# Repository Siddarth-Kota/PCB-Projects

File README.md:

This project is about designing a benchtop Lab monitor capable of monitoring noise, temperature, and humidity levels. It is connected using an ESP-32 module which manages the sensors and acts as a link
to a home internet device to monitor and graph the information.

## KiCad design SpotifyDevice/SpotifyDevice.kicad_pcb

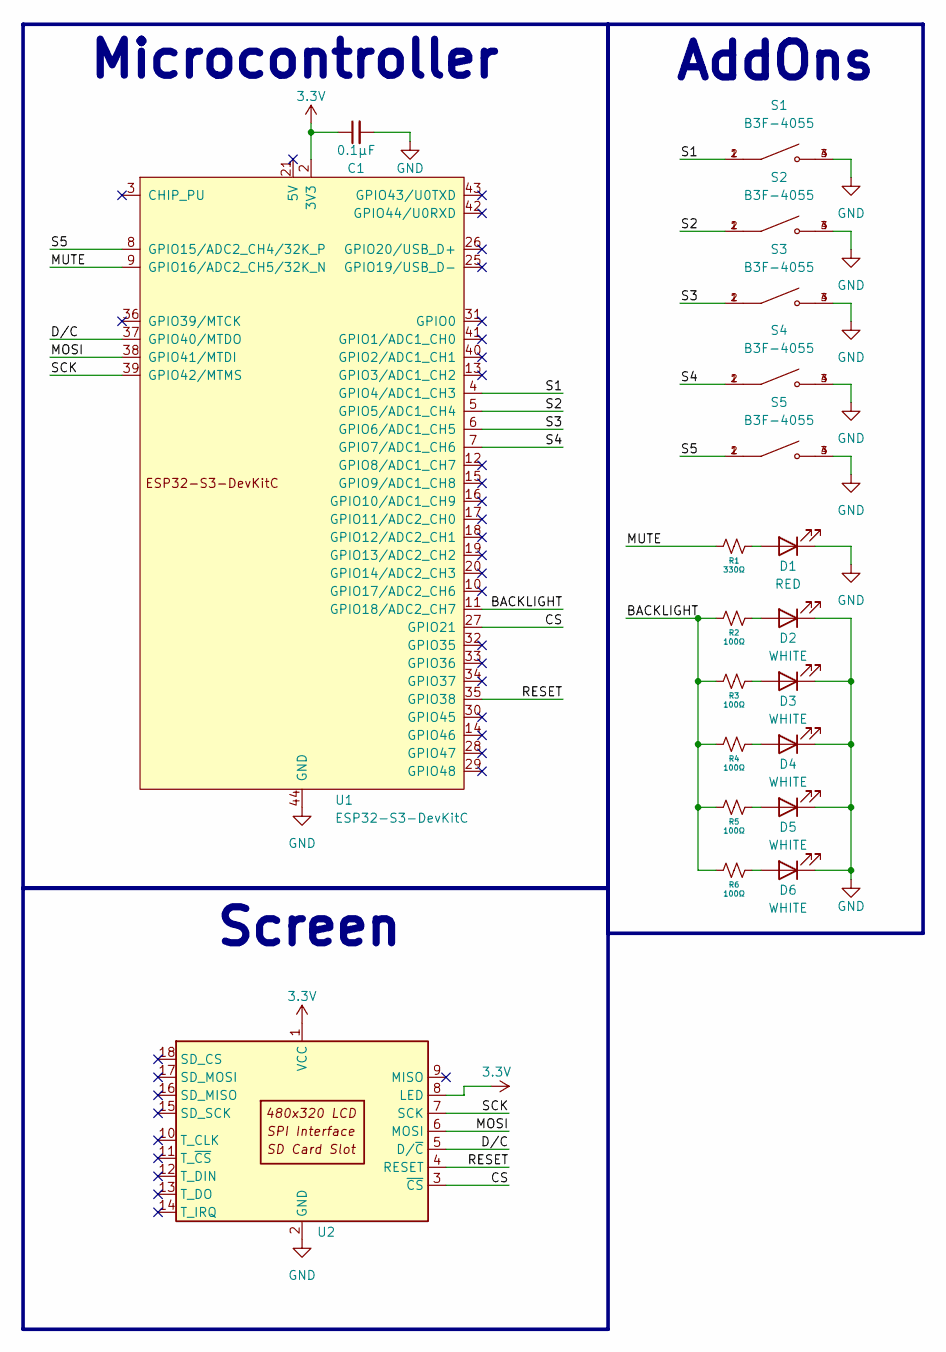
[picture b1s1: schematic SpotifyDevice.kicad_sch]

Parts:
C1: 0.1µF; C_0603_1608Metric
D1: RED; 151031SS06000
D2, D3, D4, D5, D6: WHITE; IN-S63BT5UW
R1: 330Ω; R_0603_1608Metric
R2, R3, R4, R5, R6: 100Ω; R_0603_1608Metric
S1, S2, S3, S4, S5: B3F-4055; SW_B3F-4055; PARTREV A070-E1-08
U1: ESP32-S3-DevKitC; ESP32-S3-DevKitC-1-N16R8
U2: 3.5" SPI TFT Display; 3.5_ SPI TFT Display

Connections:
3.3V: C1.1, U1.1 (3V3), U1.2 (3V3), U2.1 (VCC), U2.8 (LED)
/BACKLIGHT: R2.2, R3.2, R4.2, R5.2, R6.2, U1.11 (GPIO18/ADC2_CH7)
/CS: U1.27 (GPIO21), U2.3 (~CS)
/D/C: U1.37 (GPIO40/MTDO), U2.5 (D/~C)
/MOSI: U1.38 (GPIO41/MTDI), U2.6 (MOSI)
/MUTE: R1.2, U1.9 (GPIO16/ADC2_CH5/32K_N)
/RESET: U1.35 (GPIO38), U2.4 (RESET)
/S1: S1.1, S1.2, U1.4 (GPIO4/ADC1_CH3)
/S2: S2.1, S2.2, U1.5 (GPIO5/ADC1_CH4)
/S3: S3.1, S3.2, U1.6 (GPIO6/ADC1_CH5)
/S4: S4.1, S4.2, U1.7 (GPIO7/ADC1_CH6)
/S5: S5.1, S5.2, U1.8 (GPIO15/ADC2_CH4/32K_P)
/SCK: U1.39 (GPIO42/MTMS), U2.7 (SCK)
GND: C1.2, D1.2 (C), D2.1 (K), D3.1 (K), D4.1 (K), D5.1 (K), D6.1 (K), S1.3, S1.4, S2.3, S2.4, S3.3, S3.4, S4.3, S4.4, S5.3, S5.4, U1.22 (GND), U1.23 (GND), U1.24 (GND), U1.44 (GND), U2.2 (GND)
unnamed: D1.1 (A), R1.1
unnamed: D2.2 (A), R2.1
unnamed: D3.2 (A), R3.1
unnamed: D4.2 (A), R4.1
unnamed: D5.2 (A), R5.1
unnamed: D6.2 (A), R6.1

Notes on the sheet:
AddOns
Screen
Microcontroller

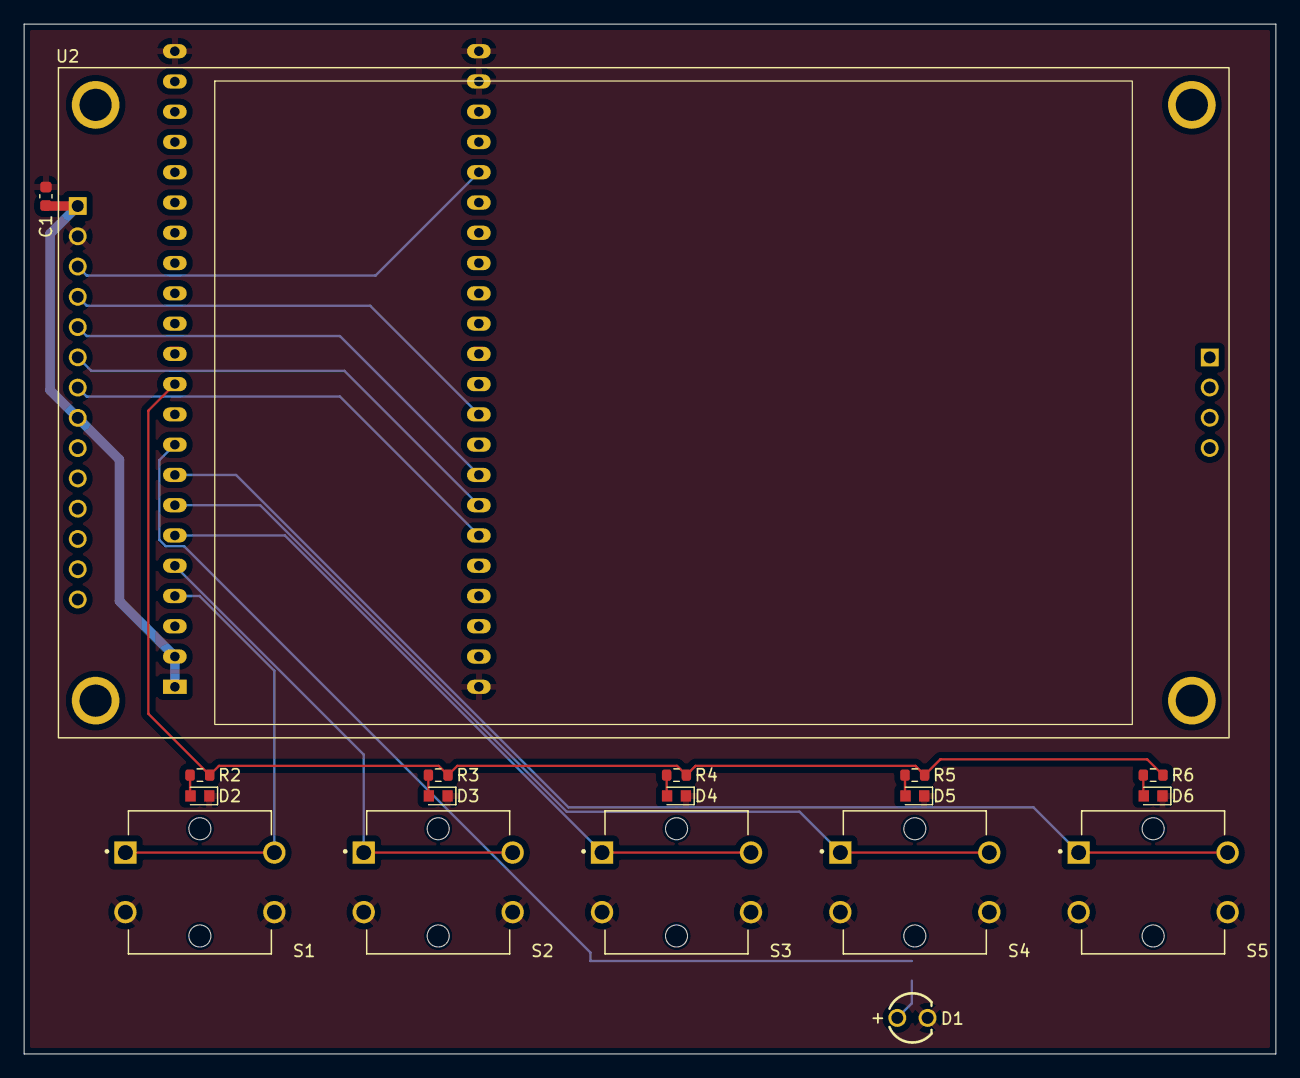
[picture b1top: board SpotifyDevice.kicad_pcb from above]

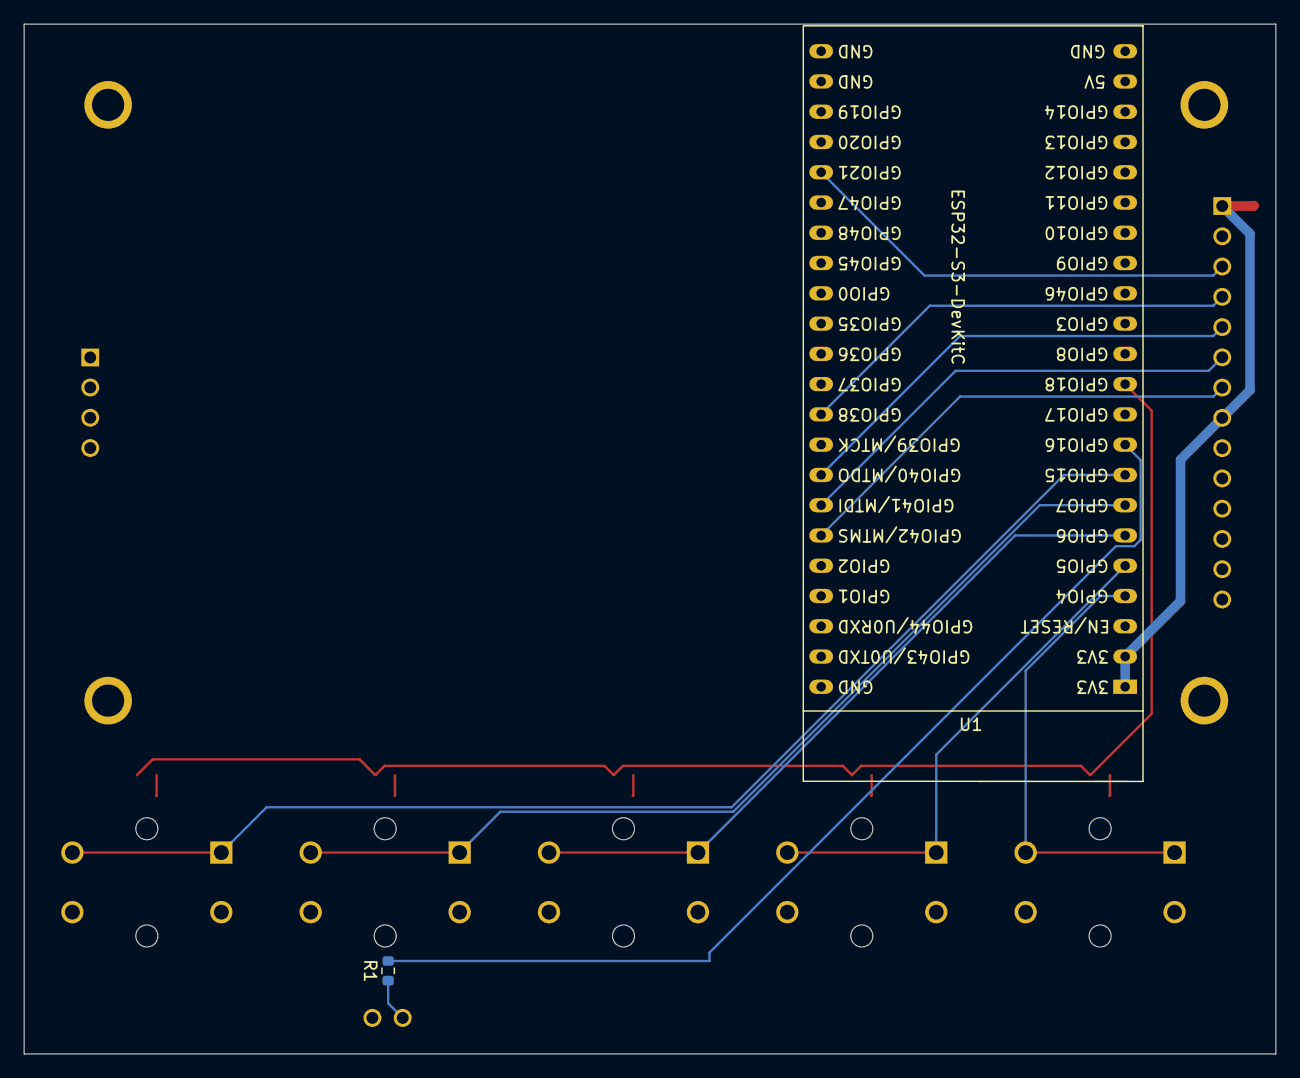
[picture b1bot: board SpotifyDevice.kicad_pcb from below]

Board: 2 copper layers, 105.1 x 86.4 mm, 20 parts (2 on the bottom side), 20 nets.

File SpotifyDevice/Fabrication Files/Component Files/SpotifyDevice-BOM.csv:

"Reference","Qty","Value","DNP","Exclude from BOM","Exclude from Board","Footprint","Datasheet"
"C1","1","0.1µF","","","","Capacitor_SMD:C_0603_1608Metric",""
"D1","1","RED","","","","ImportedParts:151031SS06000","~"
"D2,D3,D4,D5,D6","5","WHITE","","","","ImportedParts:IN-S63BT5UW","~"
"R1","1","330Ω","","","","Resistor_SMD:R_0603_1608Metric",""
"R2,R3,R4,R5,R6","5","100Ω","","","","Resistor_SMD:R_0603_1608Metric",""
"S1,S2,S3,S4,S5","5","B3F-4055","DNP","Excluded from BOM","","ImportedParts:SW_B3F-4055",""
"U1","1","ESP32-S3-DevKitC","","","","Espressif:ESP32-S3-DevKitC-1-N16R8",""
"U2","1","3.5"" SPI TFT Display","","","","ImportedParts:3.5_ SPI TFT Display",""

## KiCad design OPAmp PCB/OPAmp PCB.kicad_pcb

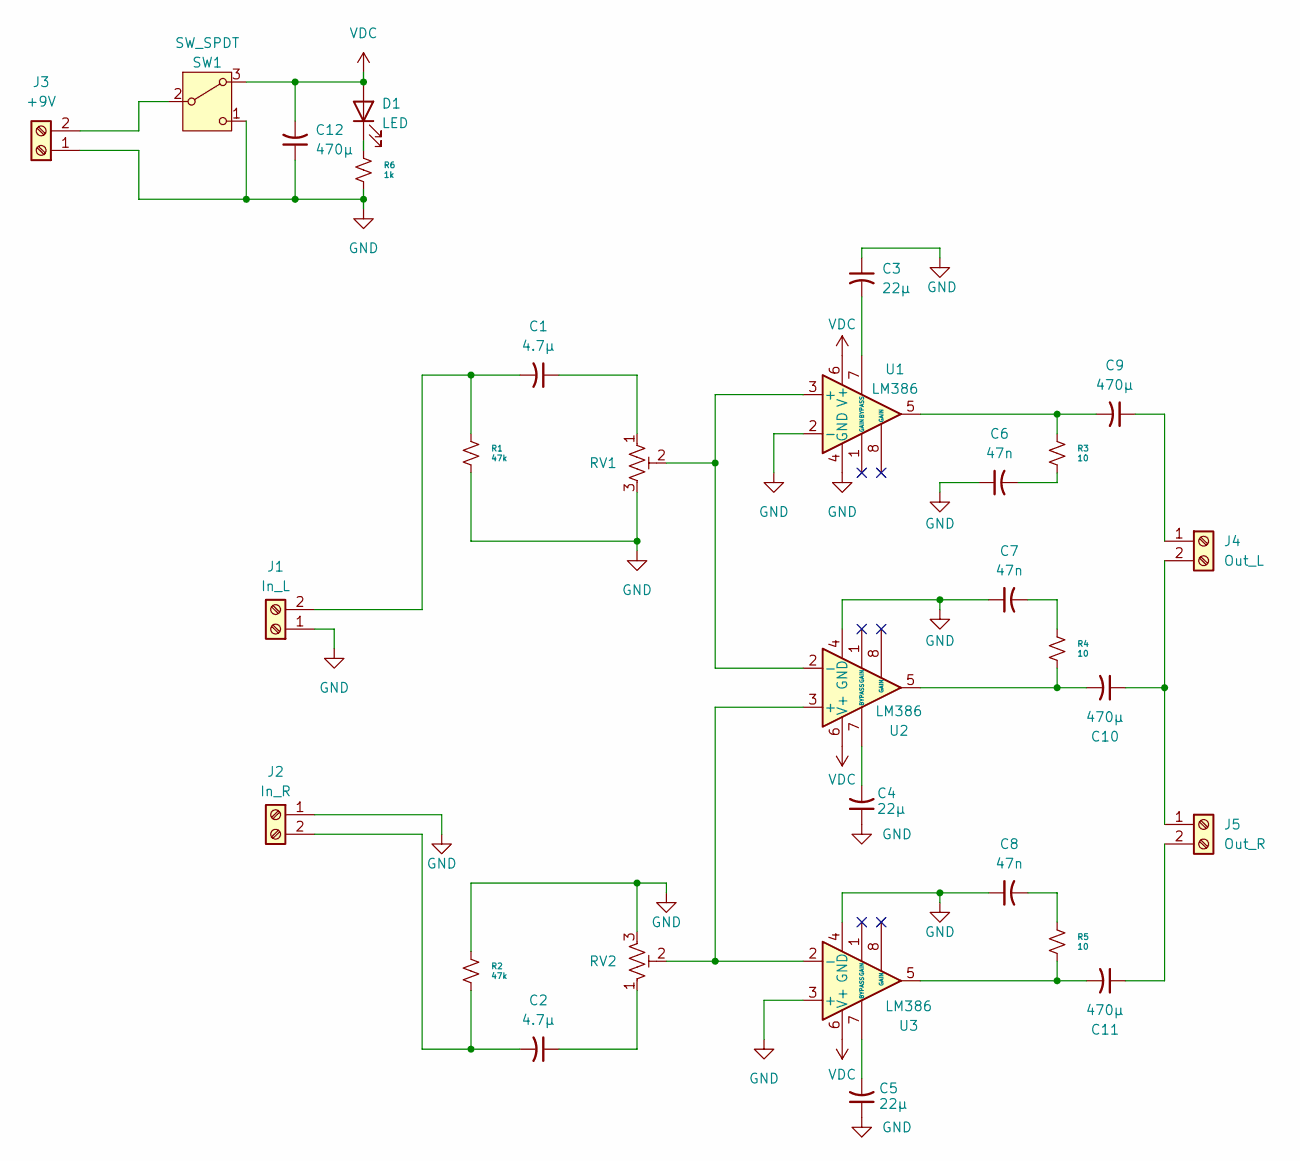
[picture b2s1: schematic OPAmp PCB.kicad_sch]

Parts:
C1, C2: 4.7μ; CP_Radial_D5.0mm_P2.50mm
C3, C4, C5: 22μ; CP_Radial_D4.0mm_P2.00mm
C6, C7, C8: 47n; C_Disc_D5.0mm_W2.5mm_P2.50mm
C9, C10, C11, C12: 470μ; CP_Radial_D10.0mm_P7.50mm
D1: LED; LED_D3.0mm
J1: In_L; TerminalBlock_MaiXu_MX126-5.0-02P_1x02_P5.00mm
J2: In_R; TerminalBlock_MaiXu_MX126-5.0-02P_1x02_P5.00mm
J3: +9V; TerminalBlock_MaiXu_MX126-5.0-02P_1x02_P5.00mm
J4: Out_L; TerminalBlock_MaiXu_MX126-5.0-02P_1x02_P5.00mm
J5: Out_R; TerminalBlock_MaiXu_MX126-5.0-02P_1x02_P5.00mm
R1, R2: 47k; R_Axial_DIN0207_L6.3mm_D2.5mm_P7.62mm_Horizontal
R3, R4, R5: 10; R_Axial_DIN0207_L6.3mm_D2.5mm_P7.62mm_Horizontal
R6: 1k; R_Axial_DIN0207_L6.3mm_D2.5mm_P7.62mm_Horizontal
RV1, RV2: R_Potentiometer_Trim_US; Potentiometer_Bourns_3386P_Vertical
SW1: SW_SPDT; SW_Slide-03_Wuerth-WS-SLTV_10x2.5x6.4_P2.54mm
U1, U2, U3: LM386; DIP-8_W7.62mm_LongPads

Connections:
GND: C3.1, C4.1, C5.1, C6.1, C7.1, C8.1, C12.1, J1.1, J2.1, J3.1, R1.2, R2.1, R6.2, RV1.3, RV2.3, SW1.1 (C), U1.2 (-), U1.4 (GND), U2.4 (GND), U3.3 (+), U3.4 (GND)
unnamed: C1.1, RV1.1
unnamed: C2.1, RV2.1
unnamed: C6.2, R3.2
unnamed: C7.2, R4.1
unnamed: C8.2, R5.1
unnamed: C9.2, R3.1, U1.5
unnamed: C10.2, R4.2, U2.5
unnamed: C11.2, R5.2, U3.5
unnamed: D1.2 (C), R6.1
unnamed: C1.2, J1.2, R1.1
unnamed: C2.2, J2.2, R2.2
unnamed: J3.2, SW1.2 (B)
unnamed: C9.1, J4.1
unnamed: C10.1, J4.2, J5.1
unnamed: C11.1, J5.2
unnamed: RV1.2, U1.3 (+), U2.2 (-)
unnamed: C3.2, U1.7 (BYPASS)
unnamed: RV2.2, U2.3 (+), U3.2 (-)
unnamed: C4.2, U2.7 (BYPASS)
unnamed: C5.2, U3.7 (BYPASS)
VDC: C12.2, D1.1 (A), SW1.3 (A), U1.6 (V+), U2.6 (V+), U3.6 (V+)

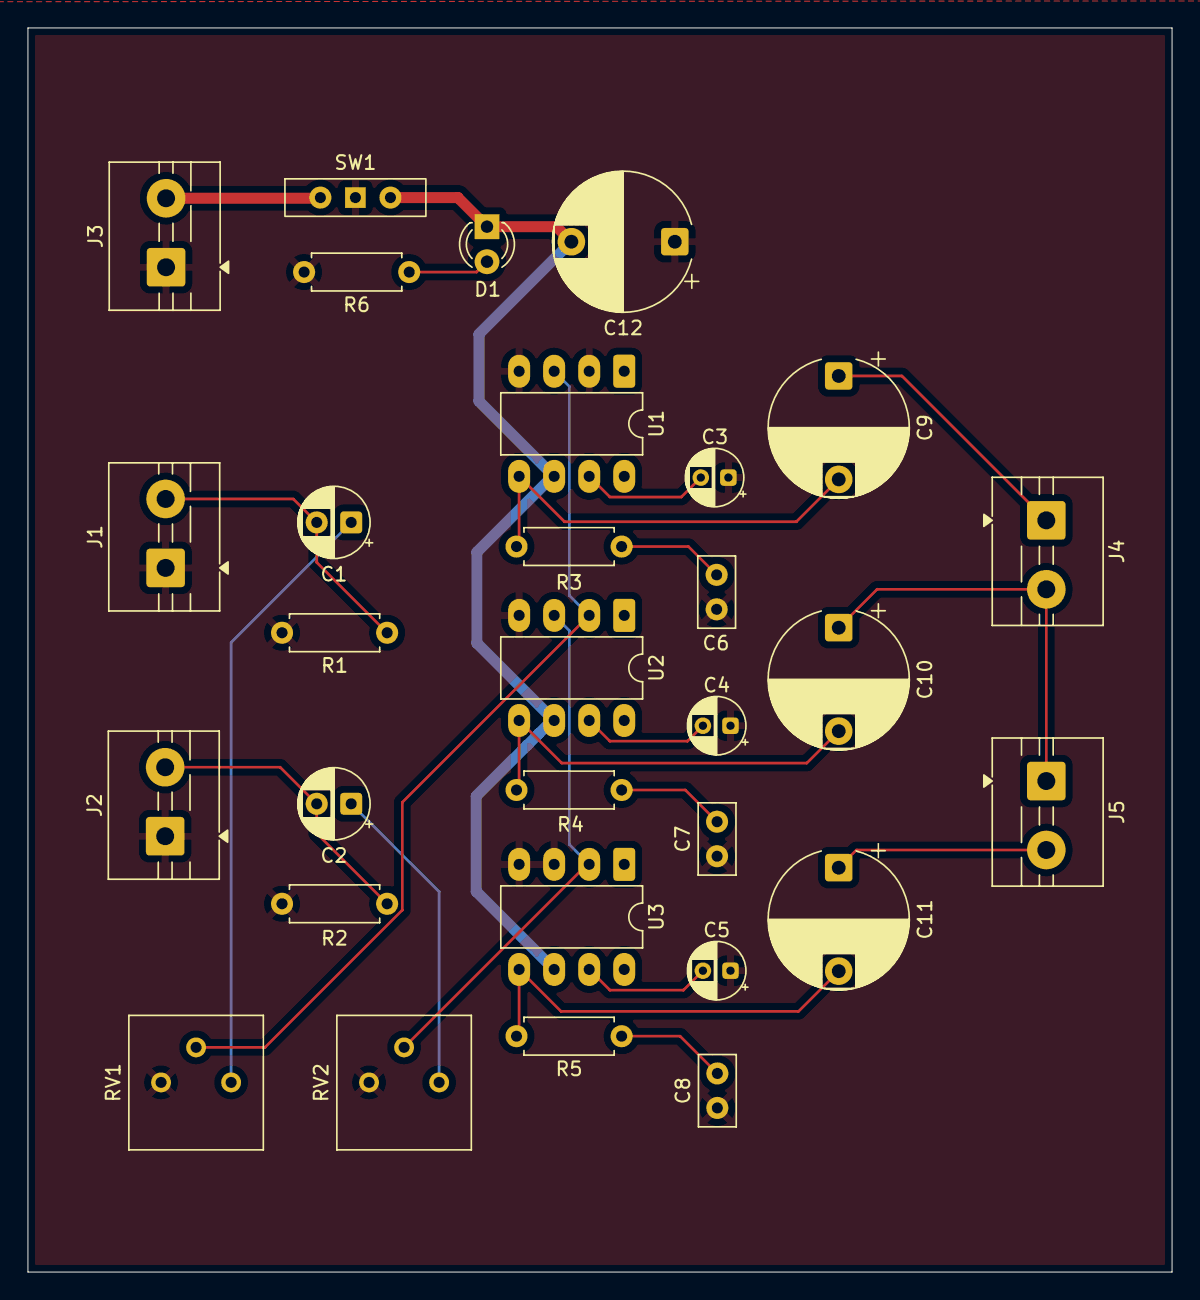
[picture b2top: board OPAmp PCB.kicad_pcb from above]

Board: 2 copper layers, 83.0 x 90.2 mm, 30 parts (0 on the bottom side), 22 nets.

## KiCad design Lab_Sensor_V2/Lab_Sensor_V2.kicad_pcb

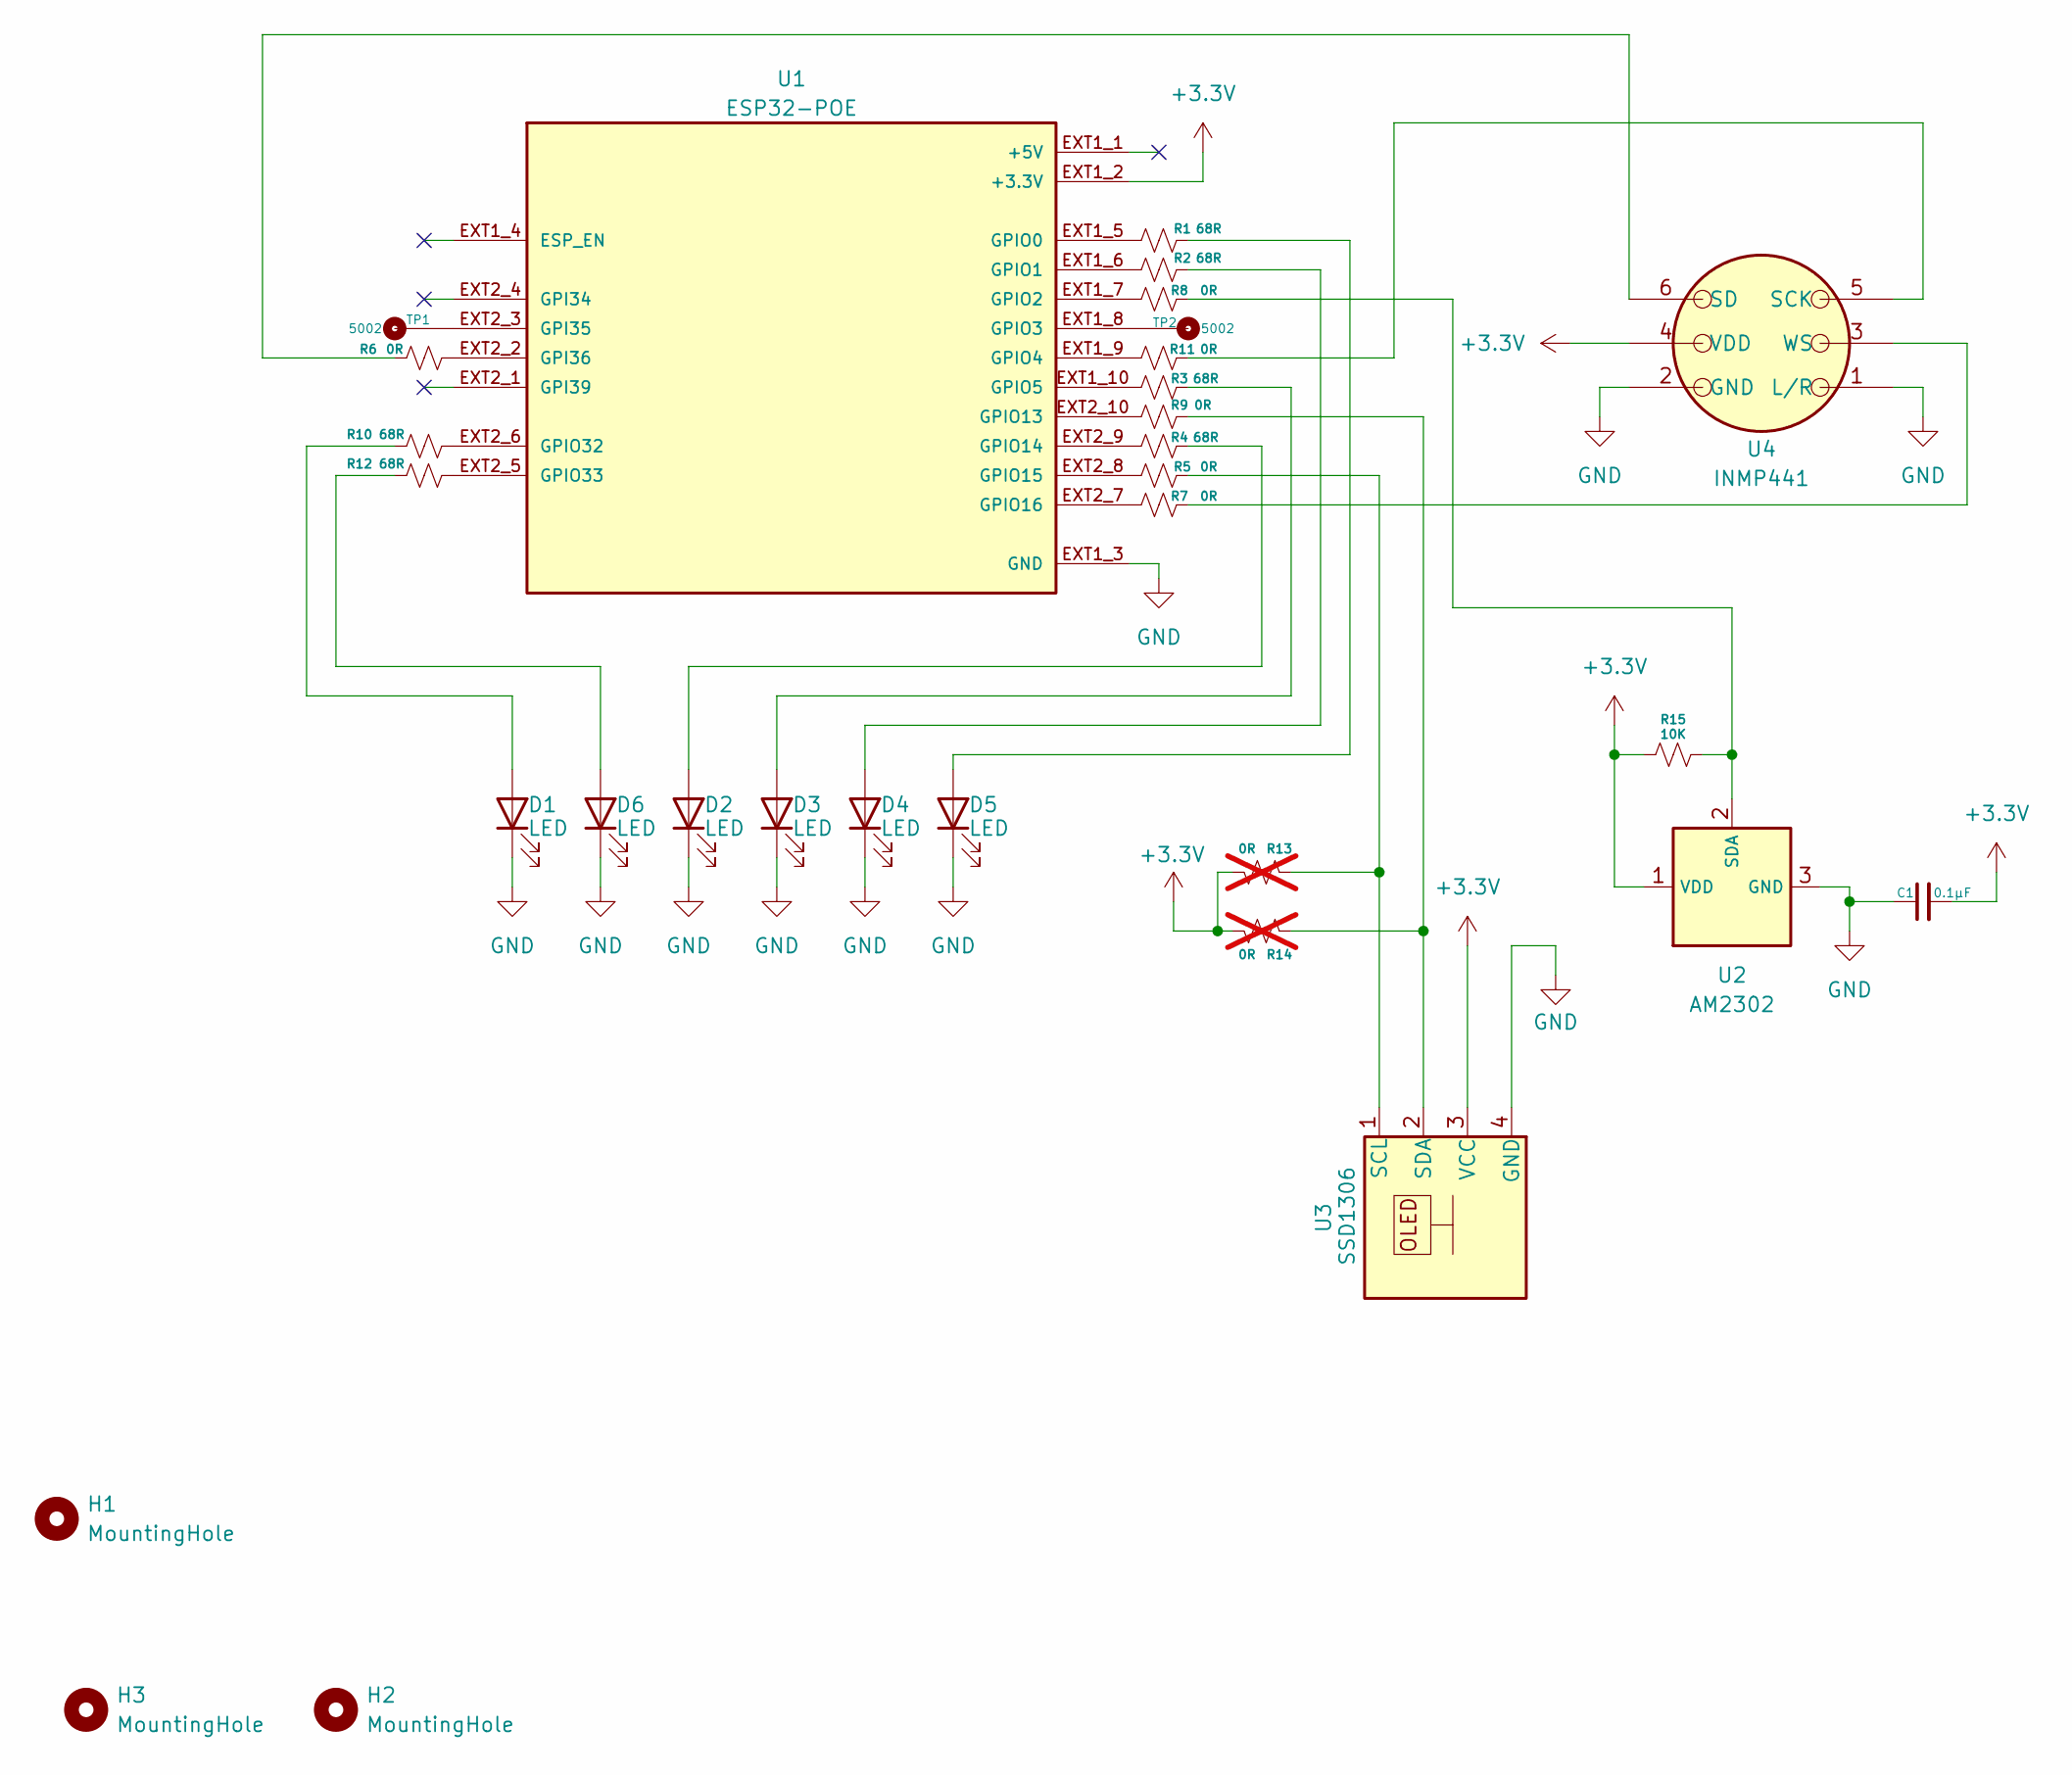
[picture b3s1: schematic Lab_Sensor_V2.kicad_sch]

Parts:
C1: 0.1µF; C_0603_1608Metric
D1, D2, D3, D4, D5, D6: LED; Standard_LED_Throughhole
H1, H2, H3: MountingHole; MountingHole_2.2mm_M2
R1, R2, R3, R4, R10, R12: 68R; R_0603_1608Metric
R5, R6, R7, R8, R9, R11: 0R; R_0603_1608Metric
R13, R14: 0R; R_0603_1608Metric; not fitted
R15: 10K; R_0603_1608Metric
TP1, TP2: 5002; PARTREV H
U1: ESP32-POE; PARTREV L1
U2: AM2302; ASAIR_AM2302_P2.54mm_Lead2.75mm_TabDown
U3: SSD1306
U4: INMP441

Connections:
+3.3V: C1.2, R13.2, R14.2, R15.2, U1.EXT1_2 (+3.3V), U2.1 (VDD), U3.3 (VCC), U4.4 (VDD)
GND: C1.1, D1.C, D2.C, D3.C, D4.C, D5.C, D6.C, U1.EXT1_3 (GND), U2.3 (GND), U2.4 (GND), U3.4 (GND), U4.1 (L/R), U4.2 (GND)
unnamed: D1.A, R10.2
unnamed: D2.A, R4.1
unnamed: D3.A, R3.1
unnamed: D4.A, R2.1
unnamed: D5.A, R1.1
unnamed: D6.A, R12.2
unnamed: TP1.TP, U1.EXT2_3 (GPI35)
unnamed: R6.1, U1.EXT2_2 (GPI36)
unnamed: R1.2, U1.EXT1_5 (GPIO0)
unnamed: R2.2, U1.EXT1_6 (GPIO1)
unnamed: R8.2, U1.EXT1_7 (GPIO2)
unnamed: TP2.TP, U1.EXT1_8 (GPIO3)
unnamed: R11.2, U1.EXT1_9 (GPIO4)
unnamed: R3.2, U1.EXT1_10 (GPIO5)
unnamed: R9.1, U1.EXT2_10 (GPIO13)
unnamed: R4.2, U1.EXT2_9 (GPIO14)
unnamed: R5.2, U1.EXT2_8 (GPIO15)
unnamed: R7.2, U1.EXT2_7 (GPIO16)
unnamed: R10.1, U1.EXT2_6 (GPIO32)
unnamed: R12.1, U1.EXT2_5 (GPIO33)
unnamed: R8.1, R15.1, U2.2 (SDA)
unnamed: R5.1, R13.1, U3.1 (SCL)
unnamed: R9.2, R14.1, U3.2 (SDA)
unnamed: R11.1, U4.5 (SCK)
unnamed: R6.2, U4.6 (SD)
unnamed: R7.1, U4.3 (WS)

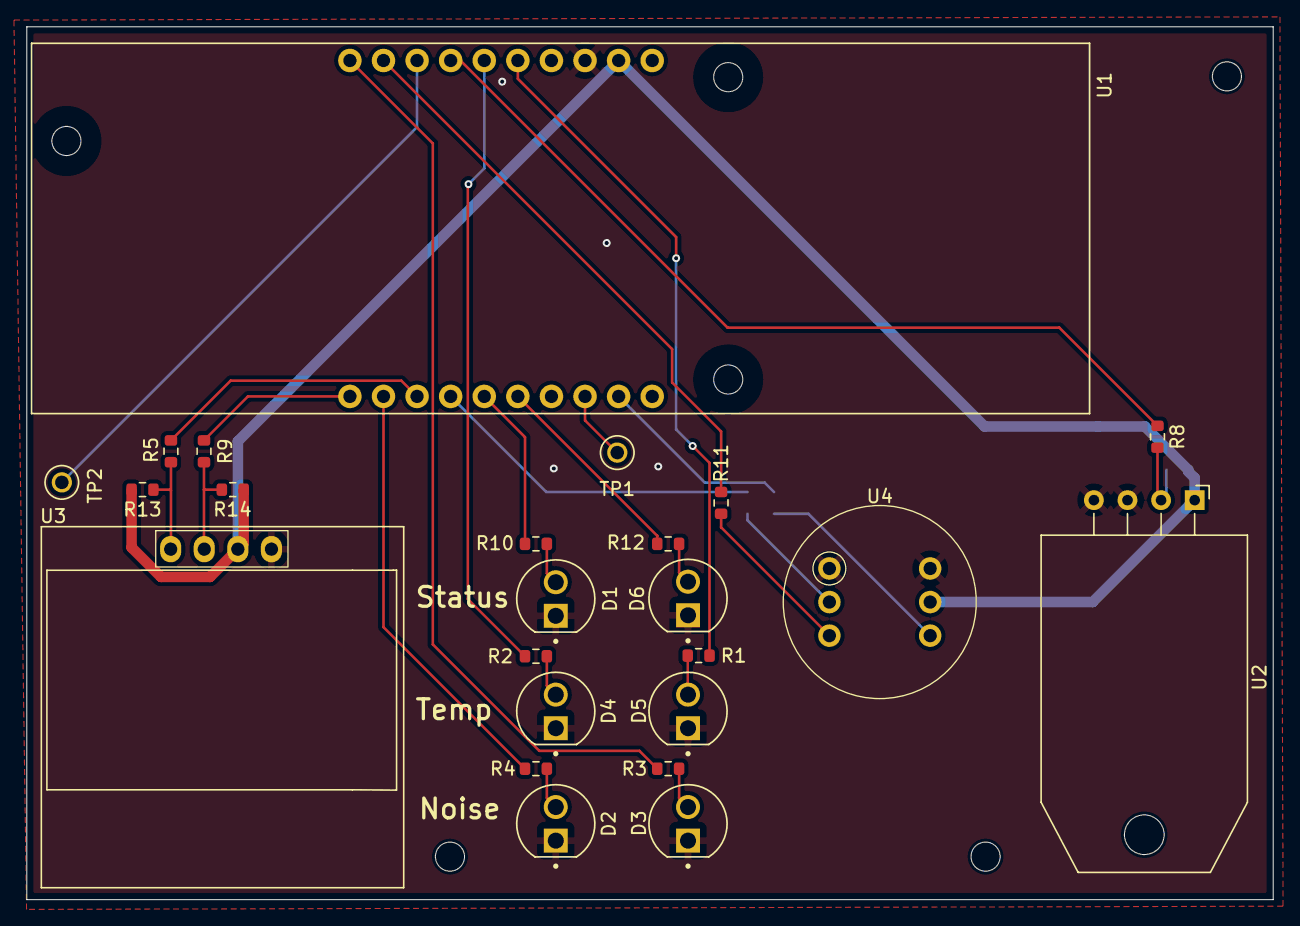
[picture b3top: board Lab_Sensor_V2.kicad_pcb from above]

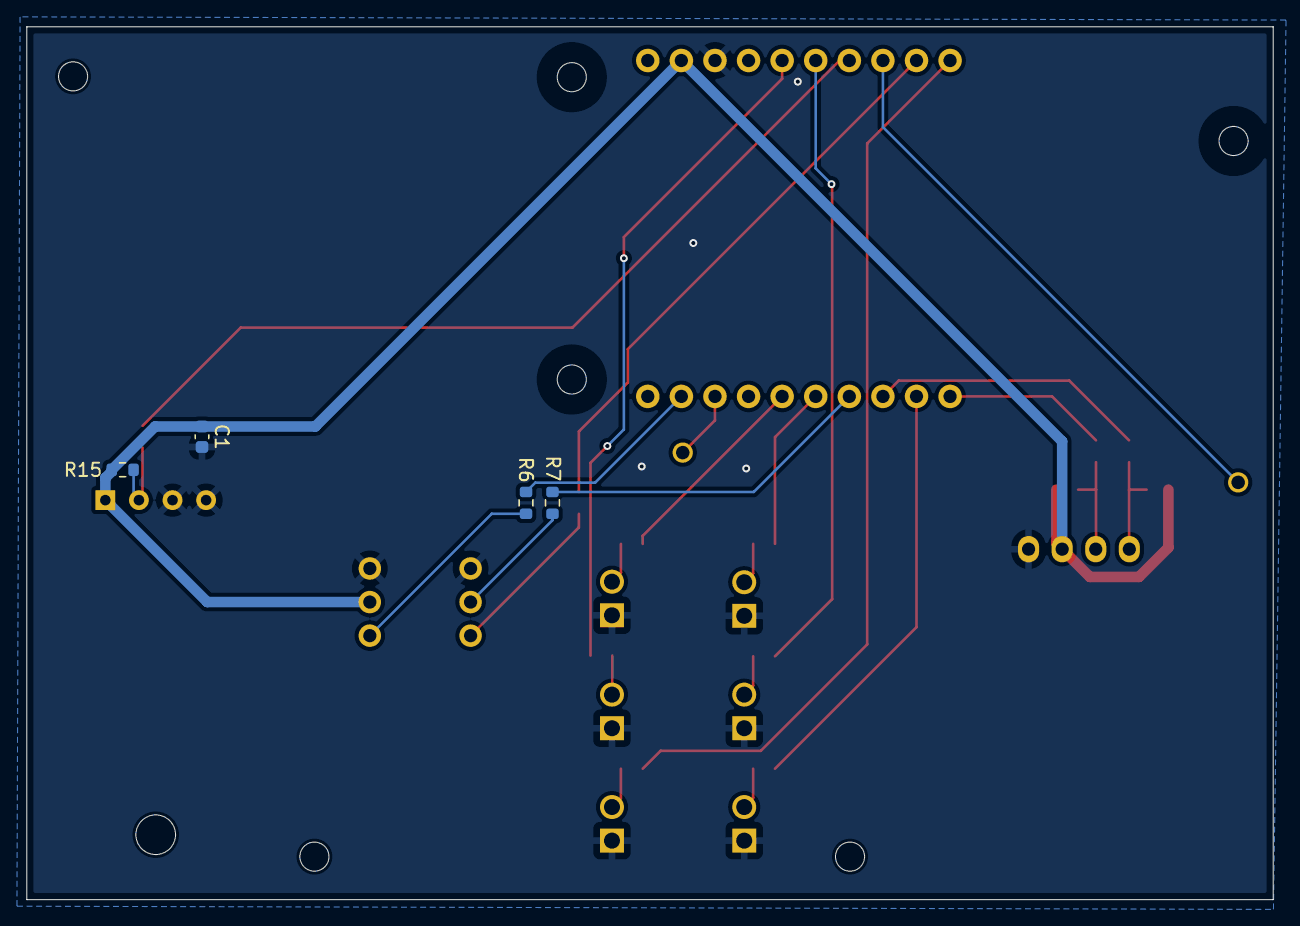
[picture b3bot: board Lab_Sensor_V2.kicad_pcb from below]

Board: 2 copper layers, 94.2 x 66.0 mm, 31 parts (4 on the bottom side), 28 nets.

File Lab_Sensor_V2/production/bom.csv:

Designator,Footprint,Quantity,Value,LCSC Part #
C1,0603,1,0.1µF,
"D1, D2, D3, D4, D5, D6",Standard_LED_Throughhole,6,LED,
"R1, R10, R12, R2, R3, R4",0603,6,68R,
"R11, R5, R6, R7, R8, R9",0603,6,0R,
R15,0603,1,10K,
"TP1, TP2",5002,2,5002,
U1,ESP32-POE,1,ESP32-POE,
U2,ASAIR_AM2302_P2.54mm_Lead2.75mm_TabDown,1,AM2302,
U3,SSD1306,1,SSD1306,
U4,INMP441,1,INMP441,

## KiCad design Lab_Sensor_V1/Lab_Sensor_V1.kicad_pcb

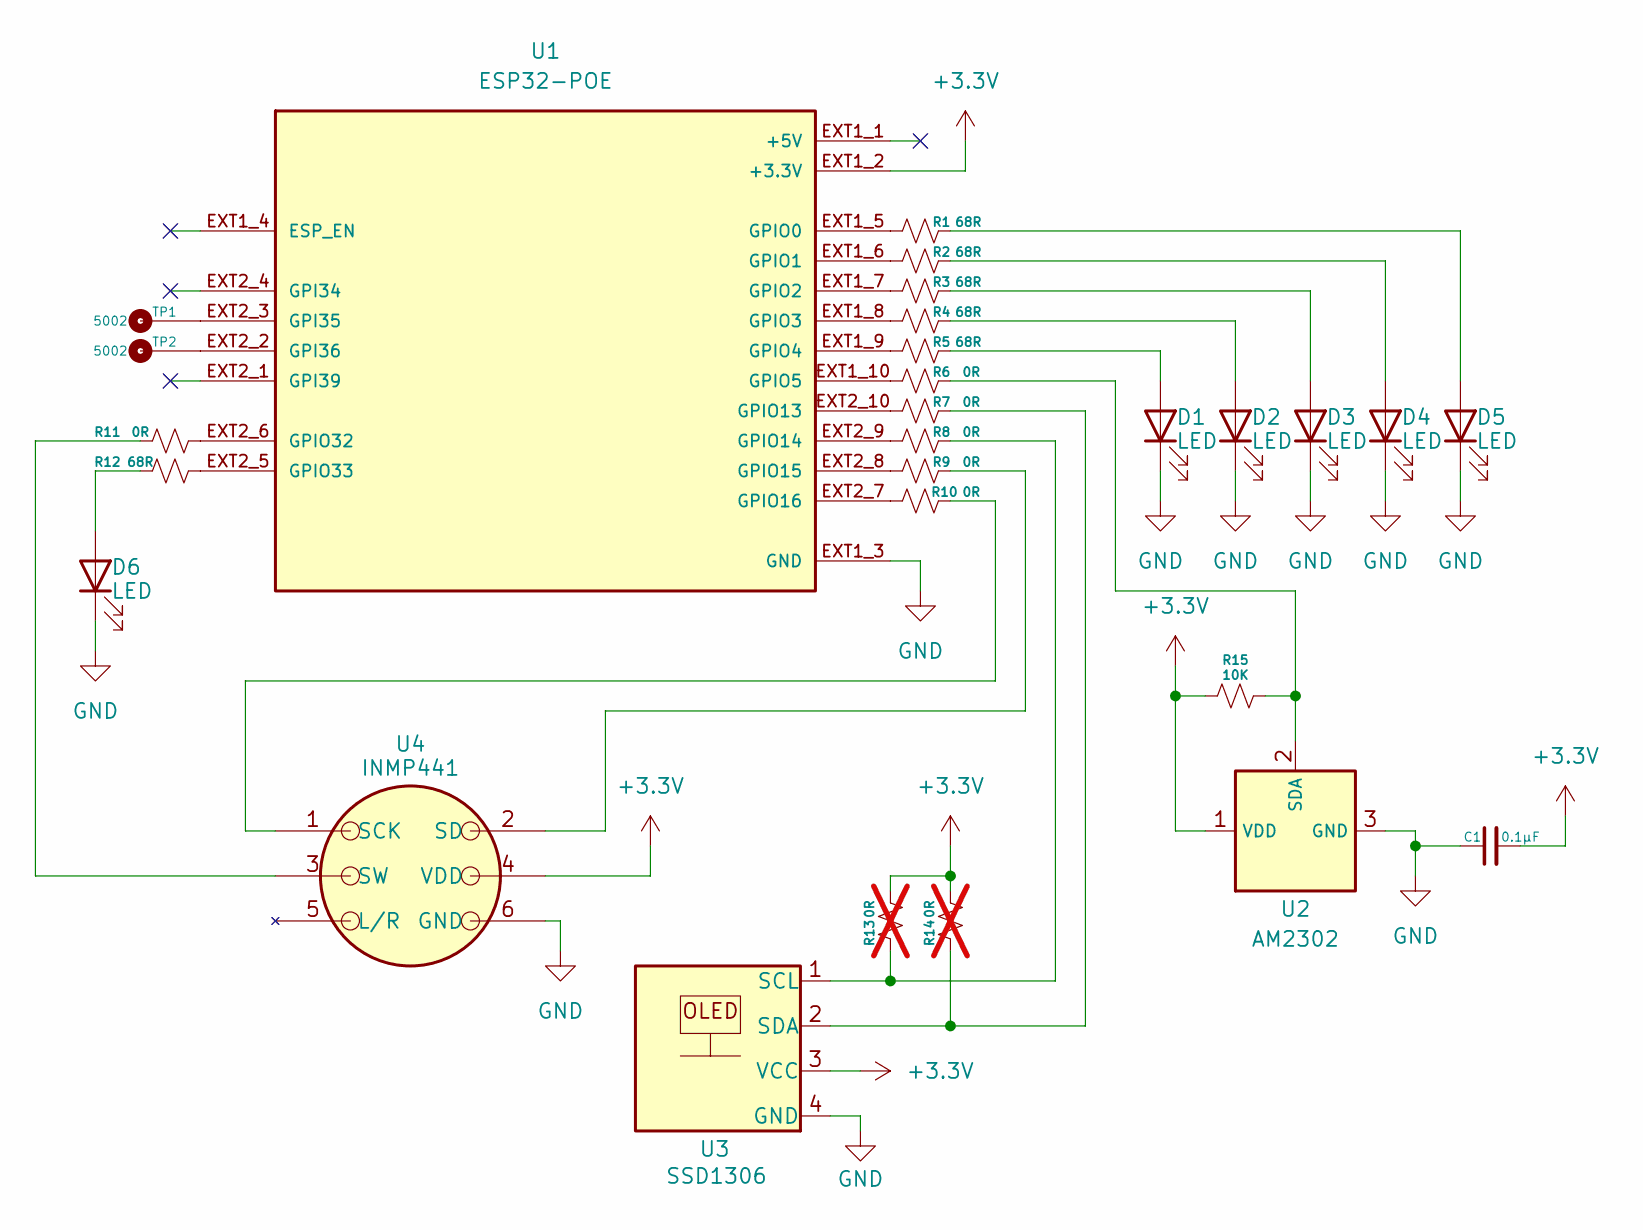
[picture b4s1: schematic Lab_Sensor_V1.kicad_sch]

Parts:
C1: 0.1µF; C_0603_1608Metric
D1, D2, D3, D4, D5, D6: LED; Standard_LED_Throughhole
R1, R2, R3, R4, R5, R12: 68R; R_0603_1608Metric
R6, R7, R8, R9, R10, R11: 0R; R_0603_1608Metric
R13, R14: 0R; R_0603_1608Metric; not fitted
R15: 10K; R_0603_1608Metric
TP1, TP2: 5002; KEYSTONE_5002; PARTREV H
U1: ESP32-POE; MODULE_ESP32-POE; PARTREV L1
U2: AM2302; ASAIR_AM2302_P2.54mm_Lead2.75mm_TabDown
U3: SSD1306; 128x64OLED
U4: INMP441

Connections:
+3.3V: C1.2, R13.1, R14.1, R15.2, U1.EXT1_2 (+3.3V), U2.1 (VDD), U3.3 (VCC), U4.4 (VDD)
GND: C1.1, D1.C, D2.C, D3.C, D4.C, D5.C, D6.C, U1.EXT1_3 (GND), U2.3 (GND), U2.4 (GND), U3.4 (GND), U4.6 (GND)
unnamed: D1.A, R5.1
unnamed: D2.A, R4.1
unnamed: D3.A, R3.1
unnamed: D4.A, R2.1
unnamed: D5.A, R1.1
unnamed: D6.A, R12.2
unnamed: TP1.TP, U1.EXT2_3 (GPI35)
unnamed: TP2.TP, U1.EXT2_2 (GPI36)
unnamed: R1.2, U1.EXT1_5 (GPIO0)
unnamed: R2.2, U1.EXT1_6 (GPIO1)
unnamed: R3.2, U1.EXT1_7 (GPIO2)
unnamed: R4.2, U1.EXT1_8 (GPIO3)
unnamed: R5.2, U1.EXT1_9 (GPIO4)
unnamed: R6.2, U1.EXT1_10 (GPIO5)
unnamed: R7.2, U1.EXT2_10 (GPIO13)
unnamed: R8.2, U1.EXT2_9 (GPIO14)
unnamed: R9.2, U1.EXT2_8 (GPIO15)
unnamed: R10.2, U1.EXT2_7 (GPIO16)
unnamed: R11.1, U1.EXT2_6 (GPIO32)
unnamed: R12.1, U1.EXT2_5 (GPIO33)
unnamed: R6.1, R15.1, U2.2 (SDA)
unnamed: R8.1, R13.2, U3.1 (SCL)
unnamed: R7.1, R14.2, U3.2 (SDA)
unnamed: R10.1, U4.1 (SCK)
unnamed: R9.1, U4.2 (SD)
unnamed: R11.2, U4.3 (SW)

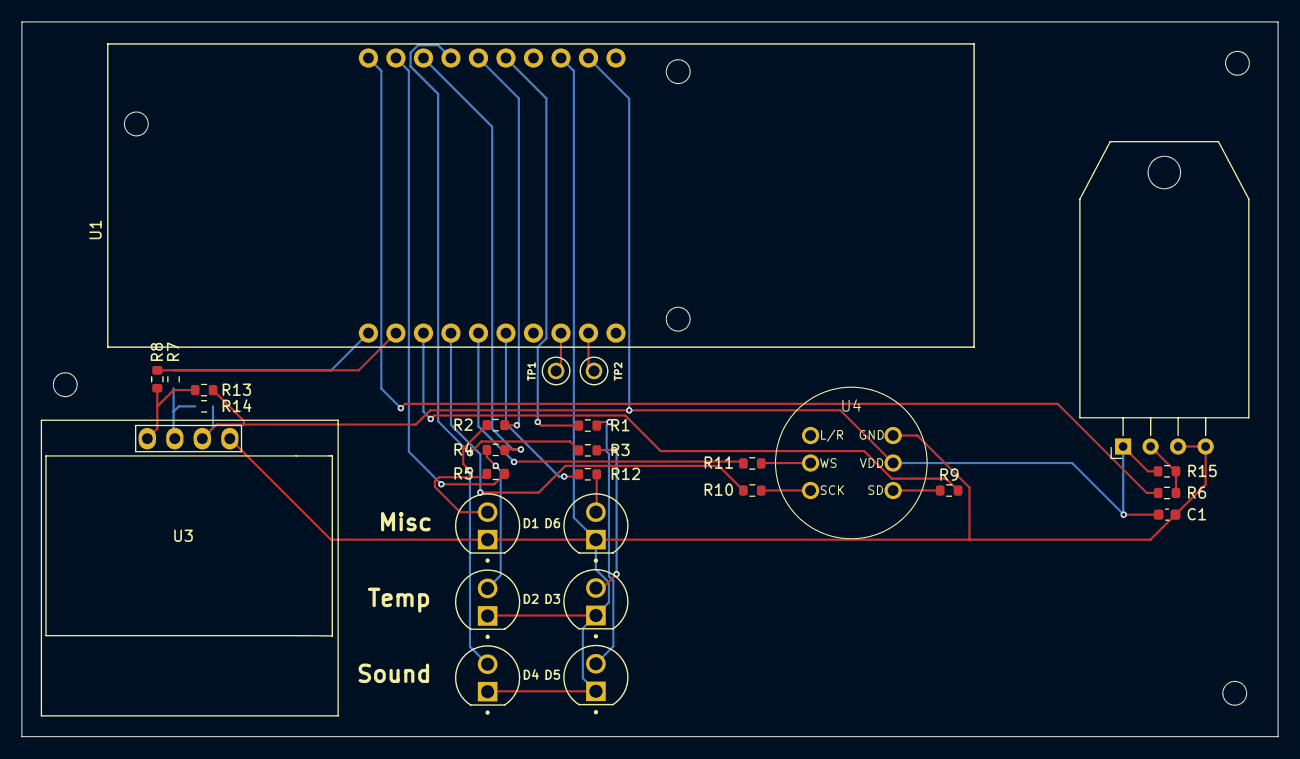
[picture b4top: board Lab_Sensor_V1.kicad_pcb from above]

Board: 2 copper layers, 116.0 x 66.0 mm, 28 parts (0 on the bottom side), 28 nets.

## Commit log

2025-07-23 Initial Lab Sensor Project Commit
2025-07-23 Fixing Version History
2025-07-23 Signals on PCB connected
2025-07-23 Routed Cables for V1
2025-07-23 Rerouted 4 GPIO expanders
2025-07-24 Cleaned up Schematic layout
2025-07-24 cleaned up PCb
2025-07-24 Updated Cad Models & Board Layout
2025-07-24 Added CAD models for render
2025-07-24 Deleted Readme
2025-07-25 improved trace sizes
2025-07-27 Changed pinout to work with Code
2025-07-28 Reorganizing files
2025-07-28 cleanup
2025-07-28 rerouted Input GPIO pins & added YAML file
2025-07-28 switched pin 5 and 36
2025-07-29 Switched pin 4 and 1
2025-07-30 Grounded L/R
2025-07-31 Added Original breadboaed code
2025-08-01 Added version 2 with tested pinout
2025-08-01 Generated Gerber Files
2025-08-03 final cleanup
2025-10-22 Started OP amp pcb
2025-11-01 Finished main circuit for schematic
2025-11-04 Finished Schematic draft 1
2025-11-04 Finished Schematic
2025-11-19 Finished PCB
2025-11-19 Pcb Saves
2025-11-22 Started Hackathon prep
2025-11-22 Moved to new Repo
2025-12-02 started keyboard PCB
2025-12-02 Edited OPAmp for submission
2025-12-14 Started Spotify Device PCB project
2025-12-14 Found Draft 1 Parts and imported Libraries
2025-12-14 Added 3D models
2025-12-14 Draft 1 of Schematic Complete
2025-12-14 Added 3D models and updated SCM
2025-12-14 updated footprints
2025-12-24 Added Footprint & Symbol for screen
2025-12-24 Added LED footprints
2025-12-24 Finished PCB and Generated Fab Files
2026-01-10 Started Code testing
2026-01-21 Troubleshooting Spotify Display Protocol
2026-01-22 Finished Code Draft 1 Without Sprites
2026-02-06 Finished Modeling for V1
2026-02-06 Rework File Structure
2026-02-06 Started V2 Design for underDesk
2026-02-09 V2 print test
2026-02-28 set up to run automatically
2026-03-09 started V3 design
2026-04-10 Drafted box V3 with better connections and support
